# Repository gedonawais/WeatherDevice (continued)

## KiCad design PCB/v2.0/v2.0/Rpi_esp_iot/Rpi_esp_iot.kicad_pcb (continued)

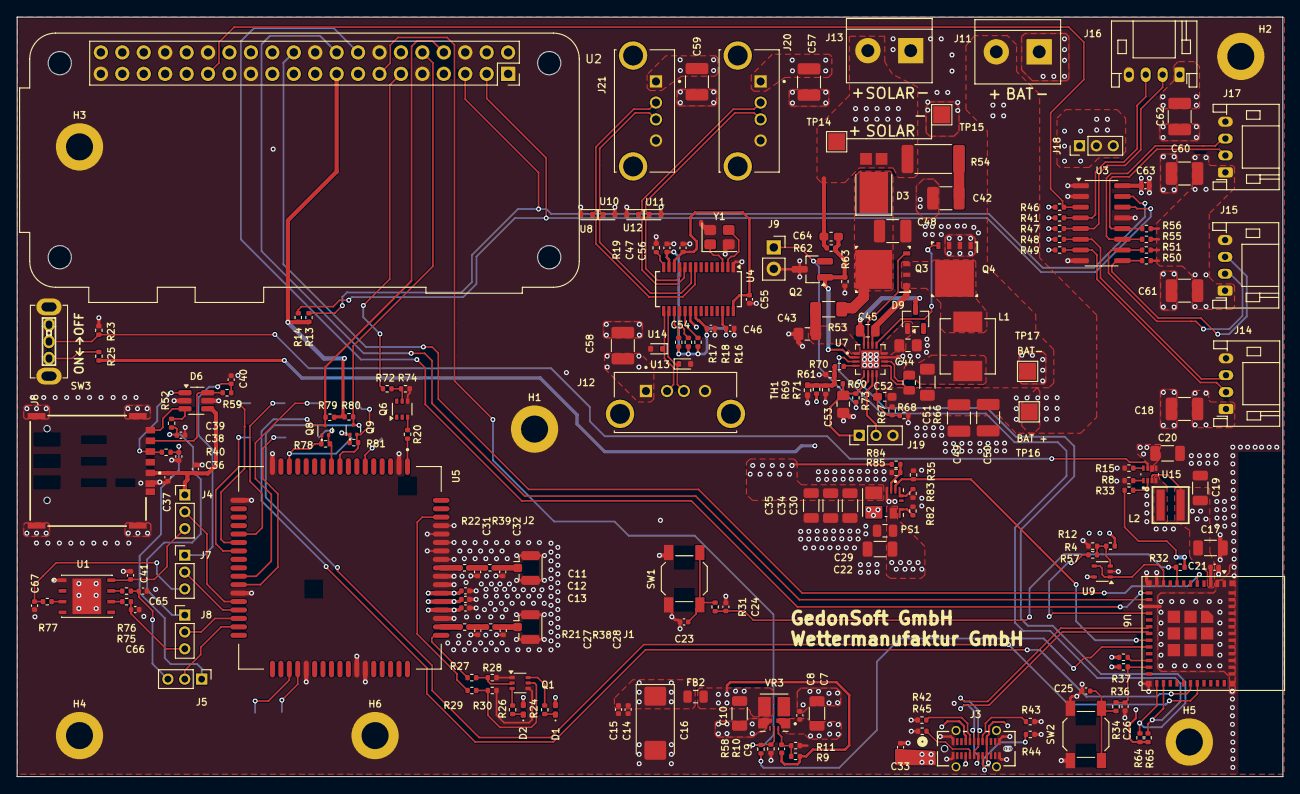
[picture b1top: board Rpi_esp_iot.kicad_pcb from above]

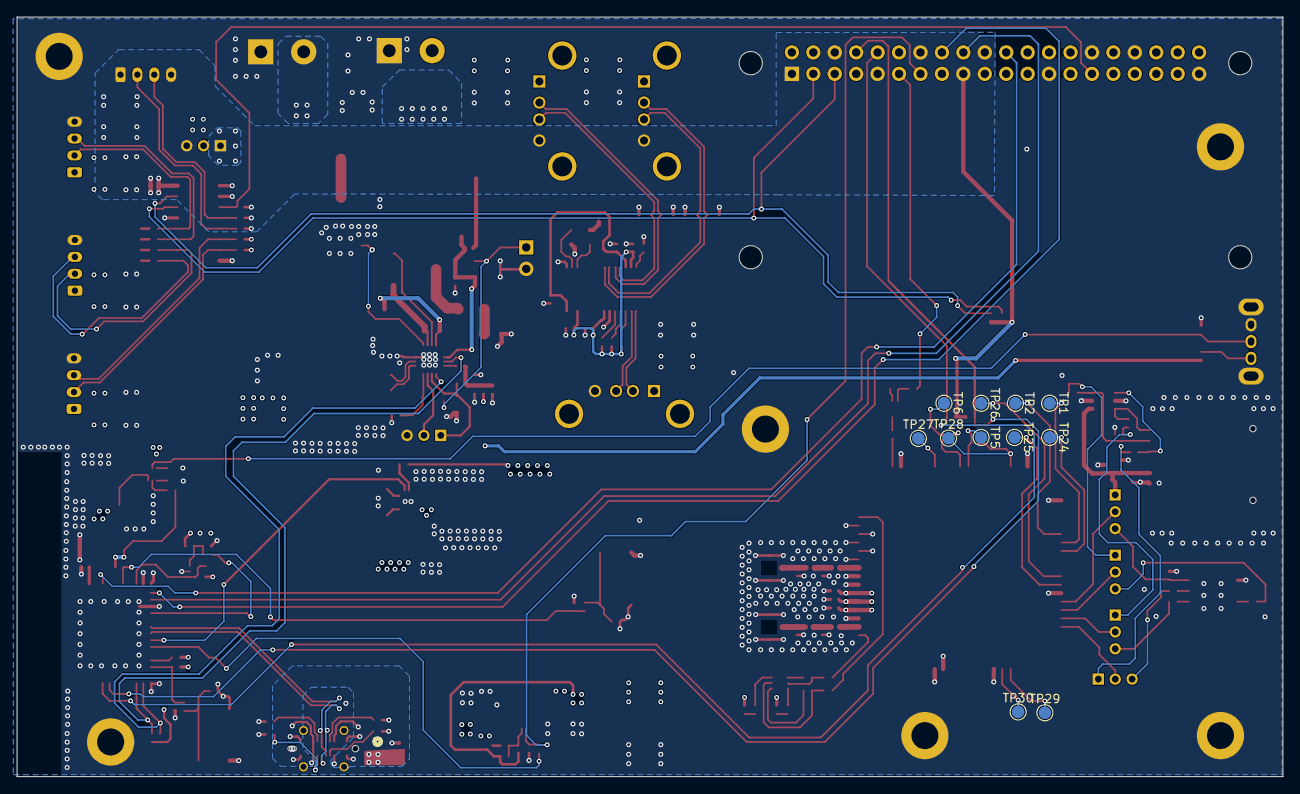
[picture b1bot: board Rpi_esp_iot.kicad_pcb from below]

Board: 4 copper layers, 150.0 x 90.0 mm, 218 parts (11 on the bottom side), 132 nets.

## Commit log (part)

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2026-04-22 all files of project
2026-04-22 updated folder
2026-06-08 update esp32 code
2026-06-08 changed the sleep time based on battery
2026-06-29 esp32 code changes
2026-06-29 esp32 code refine
